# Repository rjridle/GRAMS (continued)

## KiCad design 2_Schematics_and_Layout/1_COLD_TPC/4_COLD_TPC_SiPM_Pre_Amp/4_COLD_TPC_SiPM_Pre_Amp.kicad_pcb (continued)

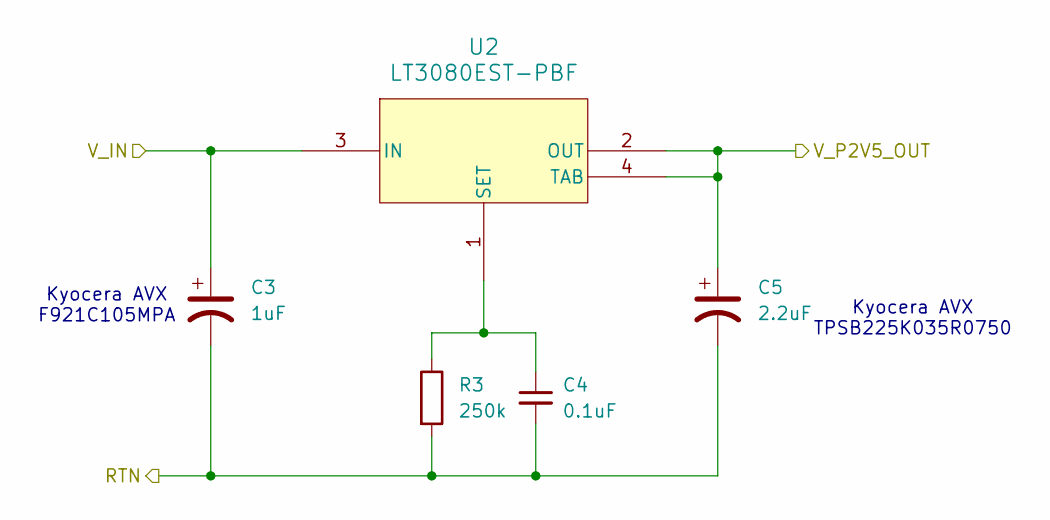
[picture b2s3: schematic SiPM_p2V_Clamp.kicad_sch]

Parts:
C3: 1uF; CP_EIA-2012-12_Kemet-R; Man. Part Num F921C105MPA
C4: 0.1uF; C_0603_1608Metric; Man. Part Num CC0603KRX7R7BB104
C5: 2.2uF; CP_EIA-3216-18_Kemet-A; Man. Part Num TAJA225K035RNJ
R3: 250k; R_0603_1608Metric; Man. Part Num P0603H2503BNT
U2: LT3080EST-PBF; SOT-3_ST_LIT; Man. Part Num LT3080EST#PBF

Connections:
/SiPM/SiPM_LV_Supply/SiPM_LV_5V/V_P5V_OUT: C3.2, C4.2, C5.2, R3.2; also elsewhere on the board
/SiPM/SiPM_LV_Supply/SiPM_LV_P3V3/V_P3V3_OUT: C3.1, U2.3 (IN); also elsewhere on the board
/SiPM/V_SiPM_LV_P2V5: C5.1, U2.2 (OUT), U2.4 (TAB); also elsewhere on the board
unnamed: C4.1, R3.1, U2.1 (SET)

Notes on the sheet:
Kyocera AVX F921C105MPA
Kyocera AVX TPSB225K035R0750

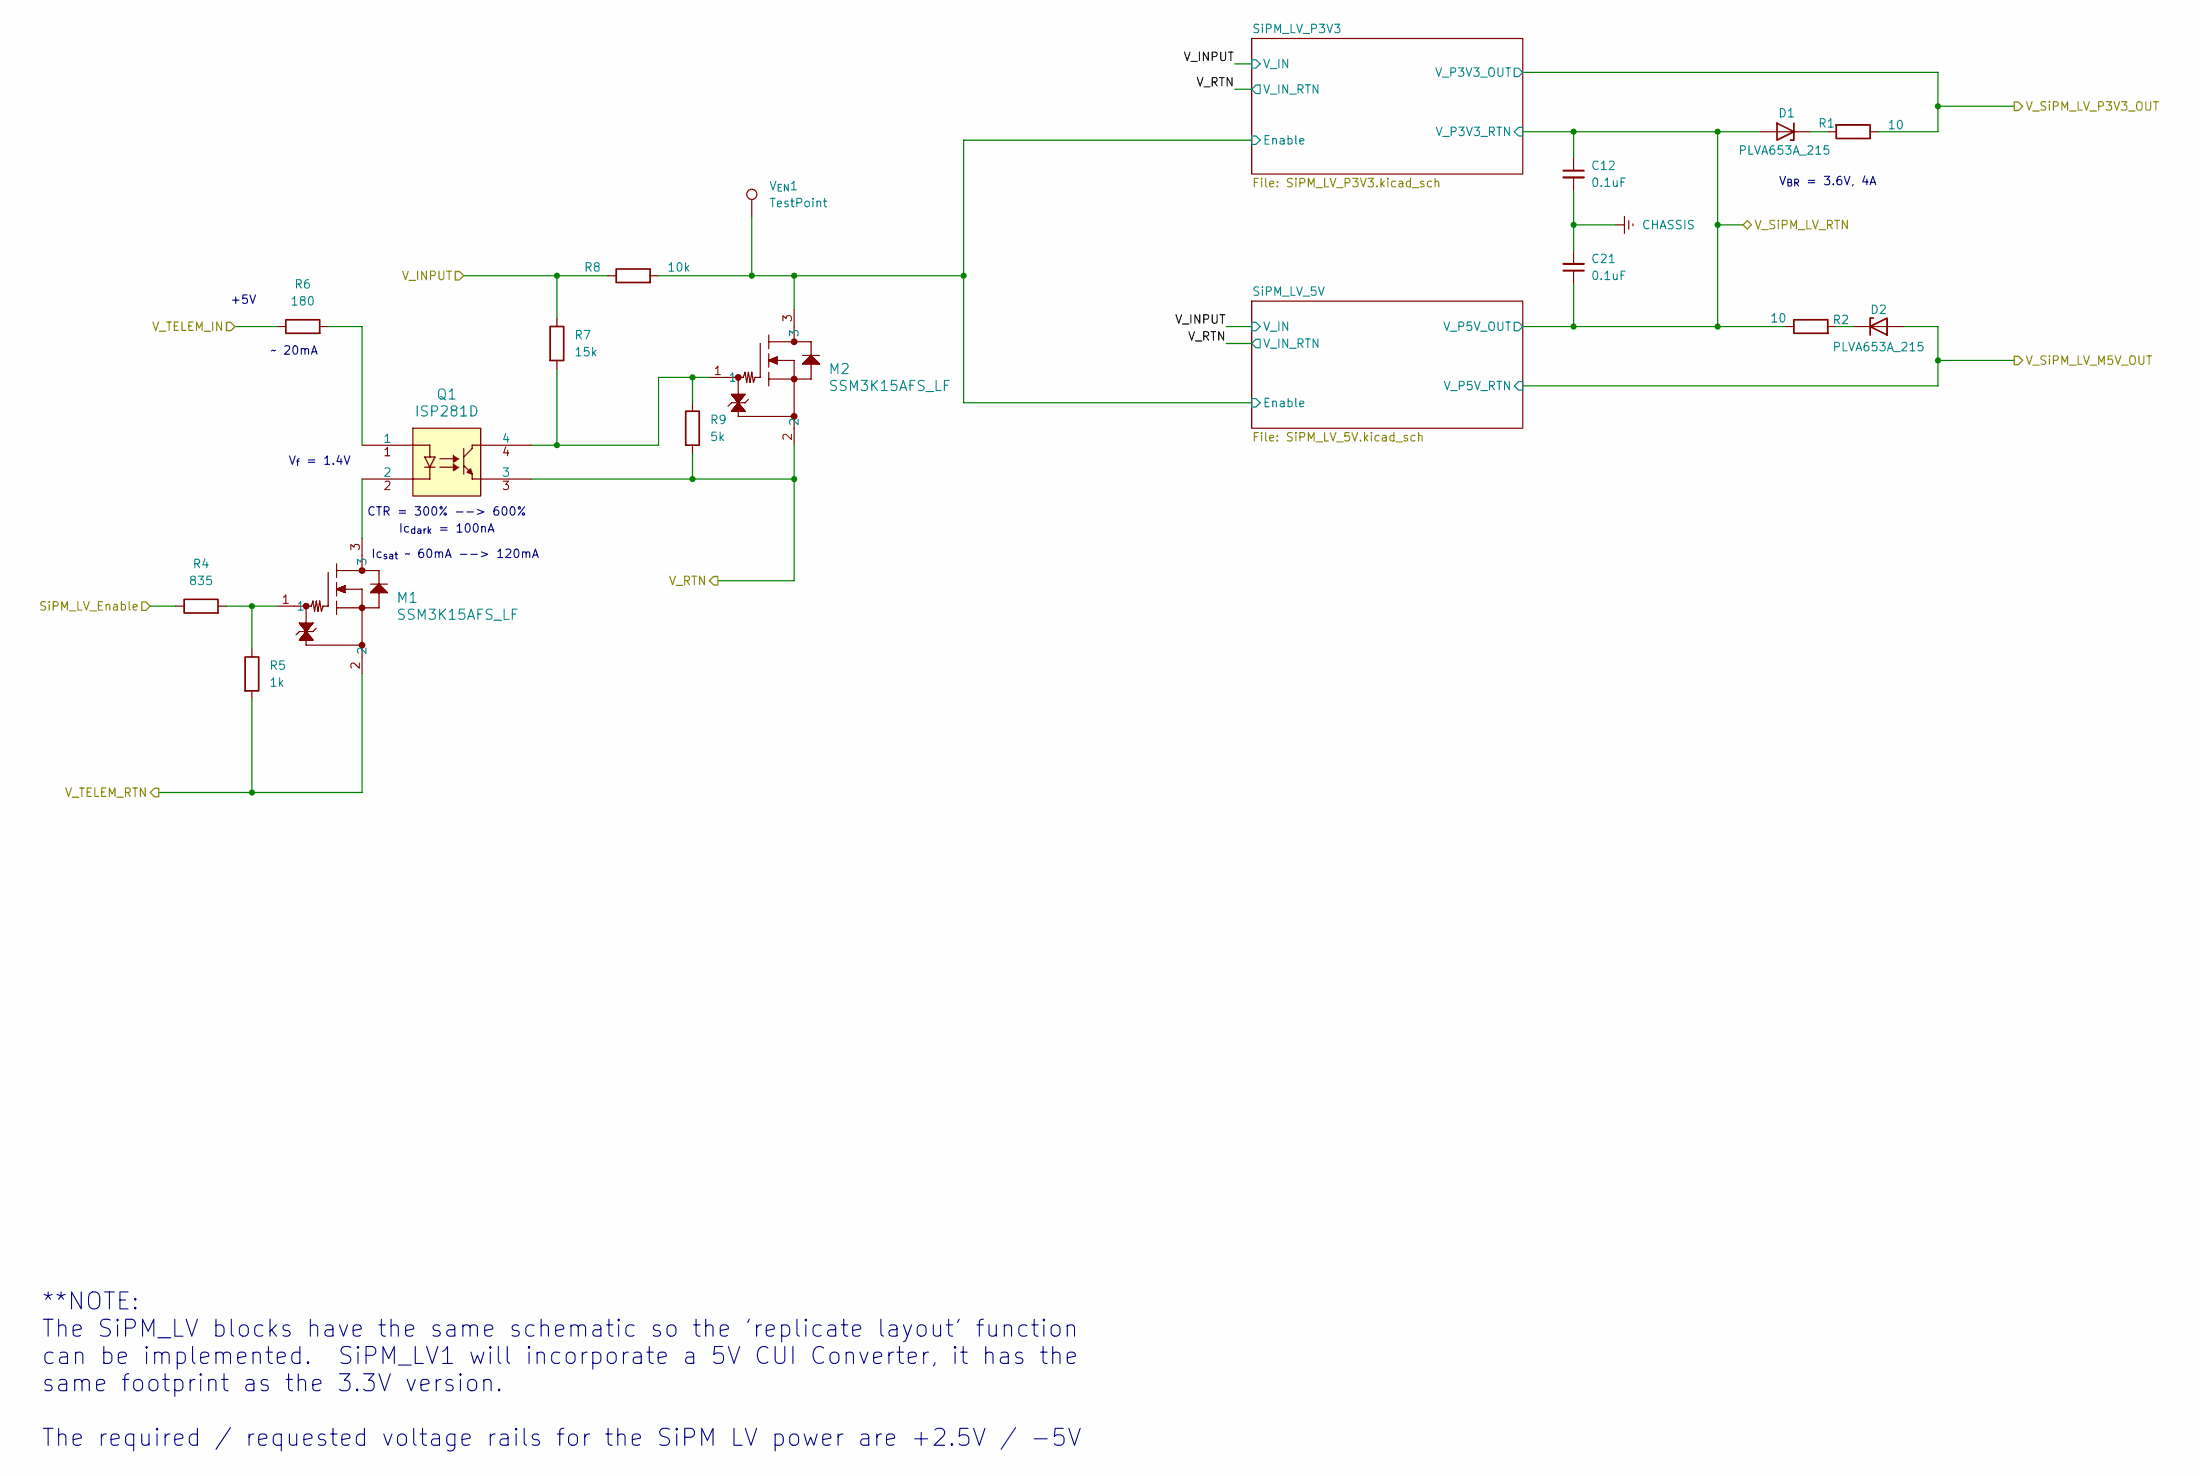
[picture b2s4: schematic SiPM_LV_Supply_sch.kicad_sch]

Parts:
C12, C21: 0.1uF; C_0603_1608Metric; Man. Part Num CC0603KRX7R7BB104
D1, D2: PLVA653A_215; SOT95P230X110-3N; Man. Part Num PLVA653A,215
M1, M2: SSM3K15AFS_LF; SSM_TOS; Man. Part Num SSM3K15AFS,LF
Q1: ISP281D; ISP281D_ISO; Man. Part Num ISP281D
R1, R2: 10; R_0603_1608Metric; Man. Part Num RMCF0603FT10R0
R4: 835; R_0603_1608Metric; Man. Part Num RN73H1JTTD8350A05
R5: 1k; R_0603_1608Metric; Man. Part Num RT0603BRD071KL
R6: 180; R_0603_1608Metric; Part Type SMD
R7: 15k; R_0603_1608Metric; Part Type SMD
R8: 10k; R_0603_1608Metric; Part Type SMD
R9: 5k; R_0603_1608Metric; Part Type SMD
V_{EN}1: TestPoint; TestPoint_Keystone_5005-5009_Compact; Man. Part Num 5008

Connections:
/P_SEC_TELEM_PWR: R6.1; also elsewhere on the board
/SEC_PWR_IN: R7.1, R8.1; also elsewhere on the board
/SEC_PWR_RTN: M2.2, Q1.3, R9.2; also elsewhere on the board
/SEC_PWR_TELEM_RTN: M1.2, R5.2; also elsewhere on the board
/SiPM/SiPM_LV_Supply/SiPM_LV_5V/Enable: M2.3, R8.2, V_{EN}1.1; also elsewhere on the board
/SiPM/SiPM_LV_Supply/SiPM_LV_5V/V_P5V_OUT: C12.1, C21.1, D1.1 (A), R2.1; also elsewhere on the board
/SiPM/SiPM_LV_Supply/SiPM_LV_Enable: R4.1; also elsewhere on the board
/SiPM/SiPM_LV_Supply/SiPM_LV_P3V3/V_P3V3_OUT: R1.1; also elsewhere on the board
/SiPM/V_SiPM_LV_M5V: D2.1 (A); also elsewhere on the board
CHASSIS: C12.2, C21.2; also elsewhere on the board
unnamed: D1.3 (K), R1.2
unnamed: D2.3 (K), R2.2
unnamed: M1.1, R4.2, R5.1
unnamed: M1.3, Q1.2
unnamed: M2.1, Q1.4, R7.2, R9.1
unnamed: Q1.1, R6.2

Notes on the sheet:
Ic_{dark} = 100nA
CTR = 300% --> 600%
~ 20mA
**NOTE: The SiPM_LV blocks have the same schematic so the 'replicate layout' function can be implemented. SiPM_LV1 will incorporate a 5V CUI Converter, it has the same footprint as the 3.3V version. The required / requested voltage rails for the SiPM LV power are +2.5V / -5V
V_{f} = 1.4V
Ic_{sat} ~ 60mA --> 120mA
+5V
V_{BR} = 3.6V, 4A

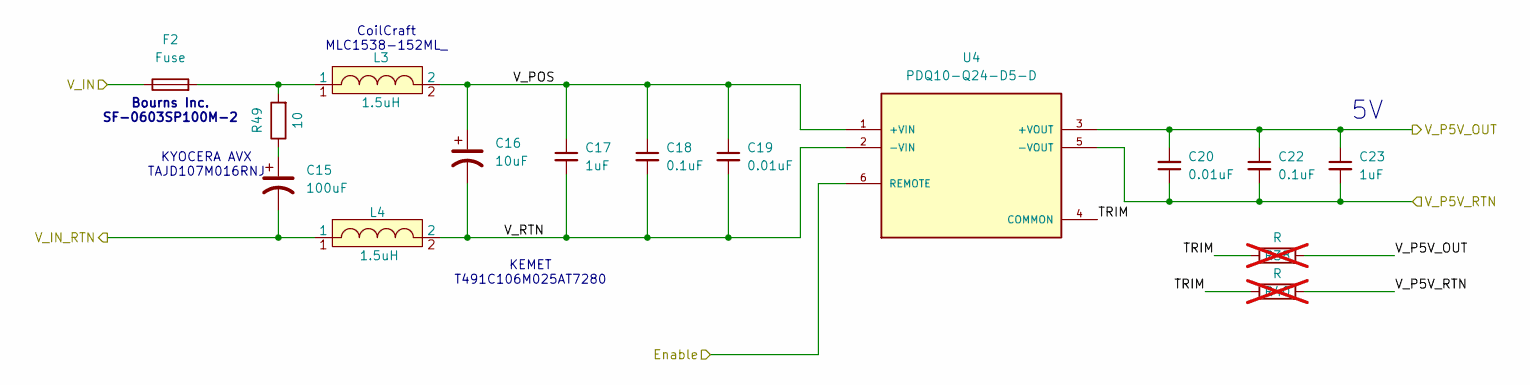
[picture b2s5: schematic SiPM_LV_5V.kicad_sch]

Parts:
C15: 100uF; CP_EIA-7343-20_Kemet-V; Man. Part Num TAJD107K016RNJ
C16: 10uF; CP_EIA-3216-12_Kemet-S; Man. Part Num T491A106M016AT
C17, C23: 1uF; C_0603_1608Metric; Man. Part Num CL10B105KO8NNNC
C18, C22: 0.1uF; C_0603_1608Metric; Man. Part Num CC0603KRX7R7BB104
C19, C20: 0.01uF; C_0603_1608Metric; Man. Part Num C0603C103K5RACTU
F2: Fuse; R_0603_1608Metric; Man. Part Num SF-0603SP100M-2
L3, L4: 1.5uH; MLC7542-311MEC; Man. Part Num MLC7540-142ME
R38, R40: R; R_0805_2012Metric; Part Type SMD; not fitted
R49: 10; R_0603_1608Metric; Man. Part Num RMCF0603FT10R0
U4: PDQ10-Q24-D5-D; CONV_PDQ10-Q24-D5-D; PARTREV 1.0

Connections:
/SEC_PWR_IN: F2.1; also elsewhere on the board
/SEC_PWR_RTN: C15.2, L4.1; also elsewhere on the board
/SiPM/SiPM_LV_Supply/SiPM_LV_5V/Enable: U4.6 (REMOTE); also elsewhere on the board
/SiPM/SiPM_LV_Supply/SiPM_LV_5V/TRIM: R38.1, R40.1, U4.4 (COMMON)
/SiPM/SiPM_LV_Supply/SiPM_LV_5V/V_P5V_OUT: C20.2, C22.1, C23.1, R38.2, U4.3 (+VOUT); also elsewhere on the board
/SiPM/SiPM_LV_Supply/SiPM_LV_5V/V_POS: C16.1, C17.1, C18.1, C19.1, L3.2, U4.1 (+VIN)
/SiPM/SiPM_LV_Supply/SiPM_LV_5V/V_RTN: C16.2, C17.2, C18.2, C19.2, L4.2, U4.2 (-VIN)
/SiPM/V_SiPM_LV_M5V: C20.1, C22.2, C23.2, R40.2, U4.5 (-VOUT); also elsewhere on the board
unnamed: C15.1, R49.1
unnamed: F2.2, L3.1, R49.2

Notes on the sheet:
CoilCraft MLC1538-152ML_
KEMET T491C106M025AT7280
Bourns Inc. SF-0603SP100M-2
KYOCERA AVX TAJD107M016RNJ

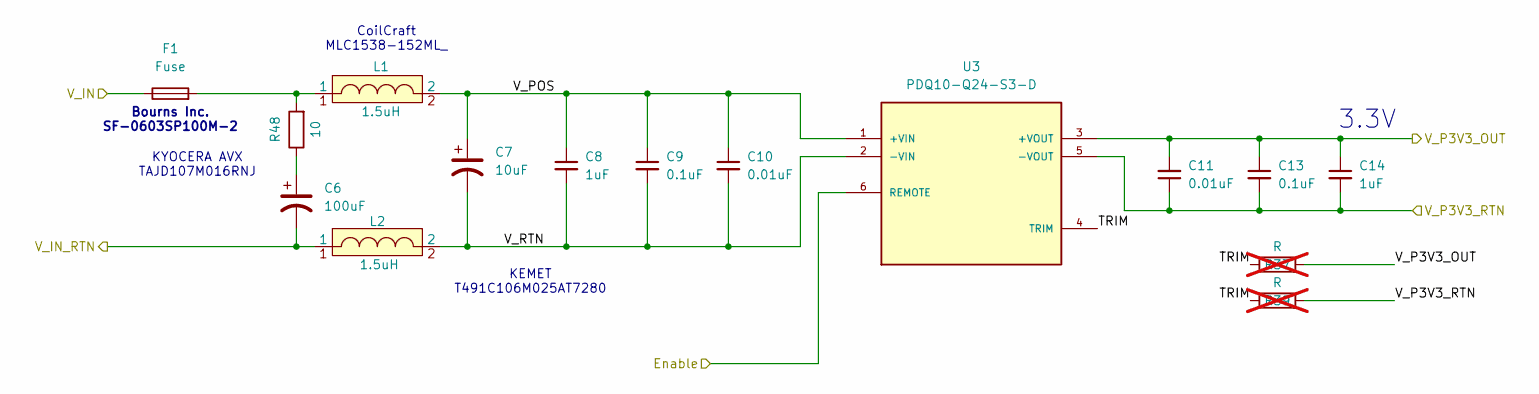
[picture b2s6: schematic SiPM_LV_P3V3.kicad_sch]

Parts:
C6: 100uF; CP_EIA-7343-20_Kemet-V; Man. Part Num TAJD107K016RNJ
C7: 10uF; CP_EIA-3216-12_Kemet-S; Man. Part Num T491A106M016AT
C8, C14: 1uF; C_0603_1608Metric; Man. Part Num CL10B105KO8NNNC
C9, C13: 0.1uF; C_0603_1608Metric; Man. Part Num CC0603KRX7R7BB104
C10, C11: 0.01uF; C_0603_1608Metric; Man. Part Num C0603C103K5RACTU
F1: Fuse; R_0603_1608Metric; Man. Part Num SF-0603SP100M-2
L1, L2: 1.5uH; MLC7542-311MEC; Man. Part Num MLC7540-142ME
R37, R39: R; R_0805_2012Metric; Part Type SMD; not fitted
R48: 10; R_0603_1608Metric; Man. Part Num RMCF0603FT10R0
U3: PDQ10-Q24-S3-D; CONV_PDQ10-Q24-S3-D; PARTREV 1.0

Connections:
/SEC_PWR_IN: F1.1; also elsewhere on the board
/SEC_PWR_RTN: C6.2, L2.1; also elsewhere on the board
/SiPM/SiPM_LV_Supply/SiPM_LV_5V/Enable: U3.6 (REMOTE); also elsewhere on the board
/SiPM/SiPM_LV_Supply/SiPM_LV_5V/V_P5V_OUT: C11.1, C13.2, C14.2, R39.2, U3.5 (-VOUT); also elsewhere on the board
/SiPM/SiPM_LV_Supply/SiPM_LV_P3V3/TRIM: R37.1, R39.1, U3.4 (TRIM)
/SiPM/SiPM_LV_Supply/SiPM_LV_P3V3/V_P3V3_OUT: C11.2, C13.1, C14.1, R37.2, U3.3 (+VOUT); also elsewhere on the board
/SiPM/SiPM_LV_Supply/SiPM_LV_P3V3/V_POS: C7.1, C8.1, C9.1, C10.1, L1.2, U3.1 (+VIN)
/SiPM/SiPM_LV_Supply/SiPM_LV_P3V3/V_RTN: C7.2, C8.2, C9.2, C10.2, L2.2, U3.2 (-VIN)
unnamed: C6.1, R48.1
unnamed: F1.2, L1.1, R48.2

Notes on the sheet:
Bourns Inc. SF-0603SP100M-2
KYOCERA AVX TAJD107M016RNJ
KEMET T491C106M025AT7280
CoilCraft MLC1538-152ML_
3.3V

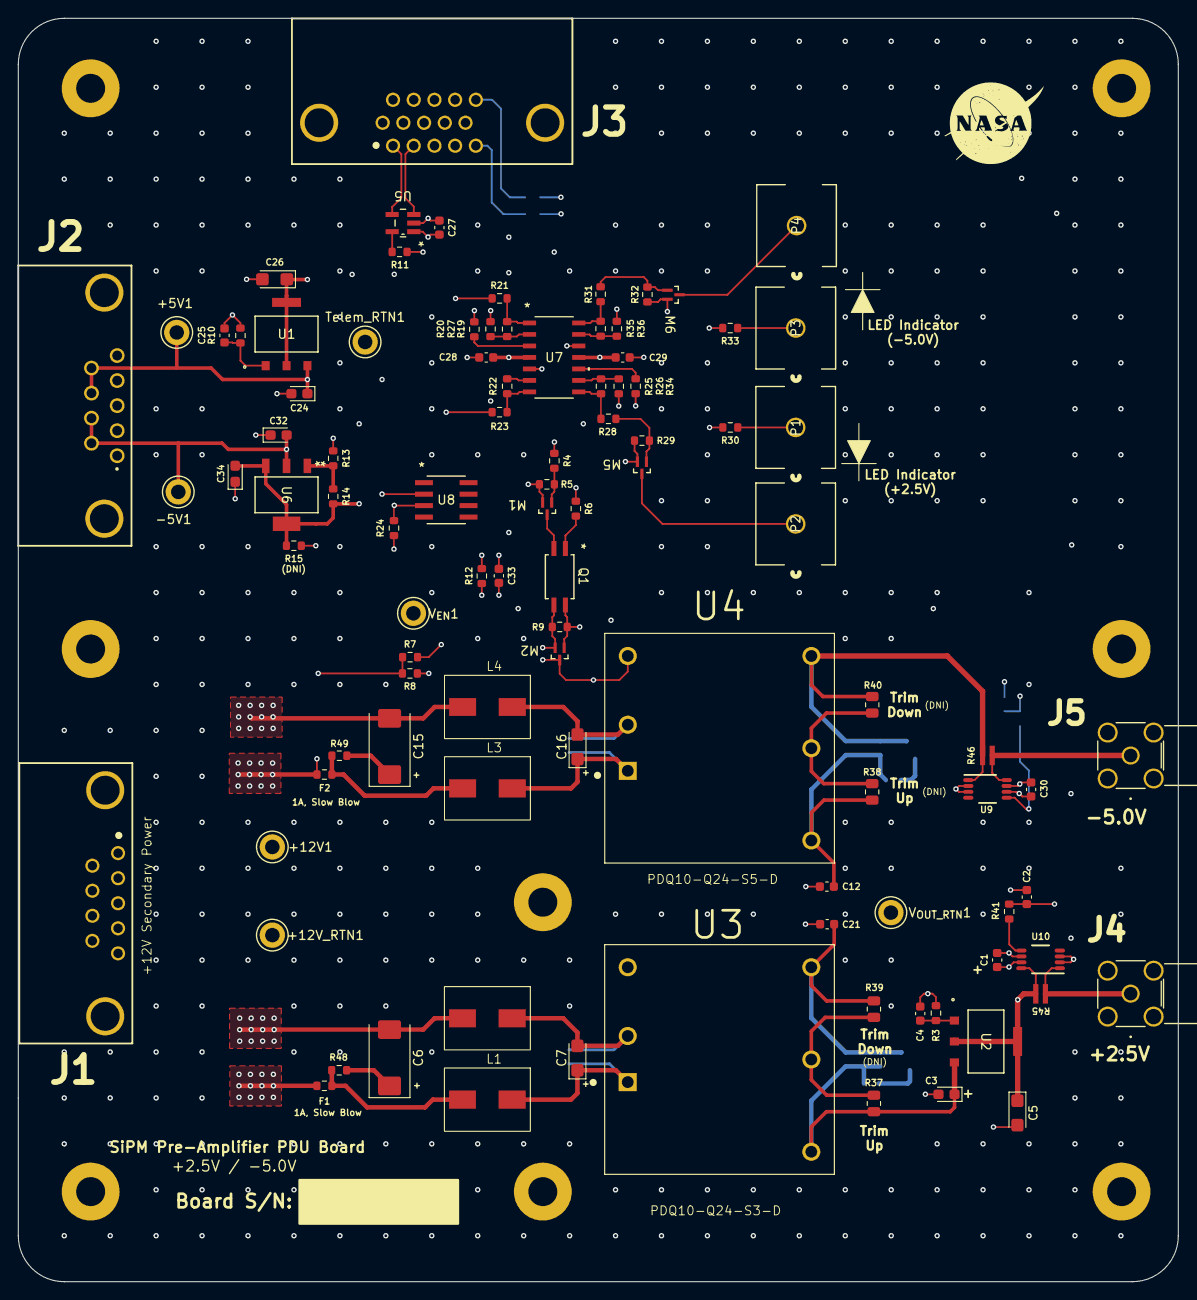
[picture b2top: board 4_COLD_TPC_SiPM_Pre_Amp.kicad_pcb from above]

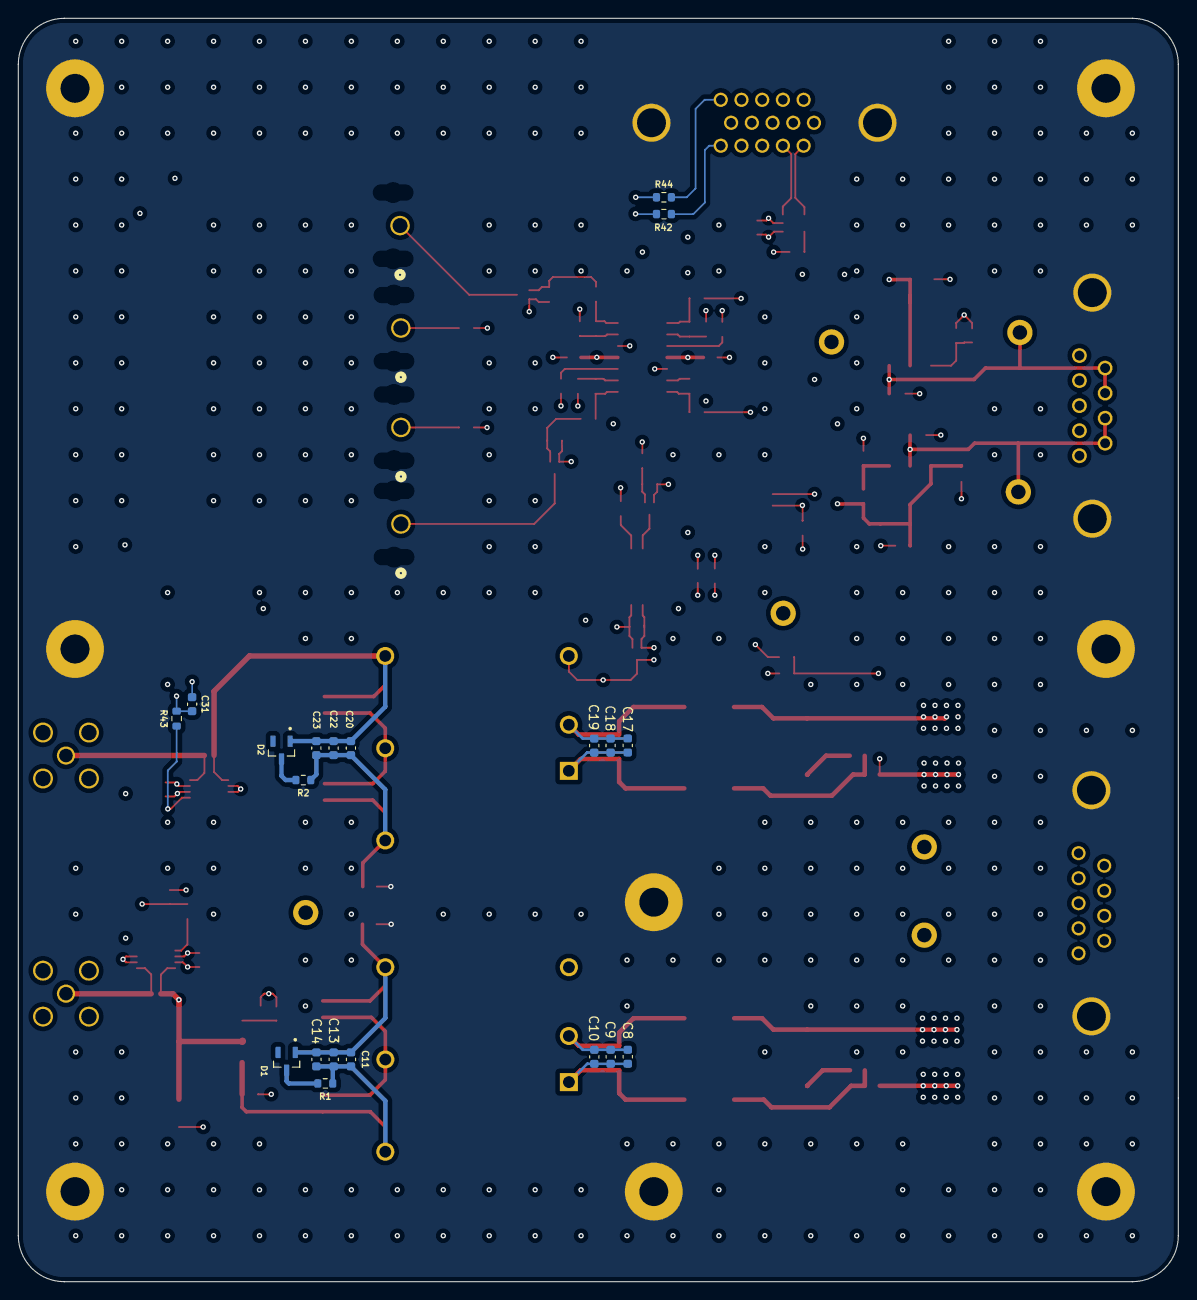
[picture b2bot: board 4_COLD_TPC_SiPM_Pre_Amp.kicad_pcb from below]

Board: 10 copper layers, 128.3 x 139.7 mm, 126 parts (20 on the bottom side), 63 nets.

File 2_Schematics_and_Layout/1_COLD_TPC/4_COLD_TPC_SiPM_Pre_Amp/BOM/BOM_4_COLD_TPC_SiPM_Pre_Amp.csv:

"Reference","Value","Footprint","Qty","DNP","Manufacturer","Man. Part Num","Distributor","Dist. Part Num"
"+5V1,+12V1","TestPoint","TestPoint:TestPoint_Keystone_5005-5009_Compact","2","","Keystone Electronics","5005","Digi-Key","36-5005-ND"
"+12V_RTN1,Telem_RTN1,V_{OUT_RTN}1","TestPoint","TestPoint:TestPoint_Keystone_5005-5009_Compact","3","","Keystone Electronics,Wurth Electronics","5006","Digi-Key","36-5006-ND"
"-5V1","TestPoint","TestPoint:TestPoint_Keystone_5005-5009_Compact","1","","Keystone Electronics","5009","Digi-Key","36-5009-ND"
"C1,C4,C9,C12,C13,C18,C21,C22,C25,C27,C28,C29,C30,C33","0.1uF","Capacitor_SMD:C_0603_1608Metric","14","","YAGEO","CC0603KRX7R7BB104","Digi-Key","311-1088-1-ND"
"C2,C8,C14,C17,C23,C31","1uF","Capacitor_SMD:C_0603_1608Metric","6","","Samsung Electro-Mechanics","CL10B105KO8NNNC","Digi-Key","1276-1019-1-ND"
"C3,C24,C32,C34","1uF","Capacitor_Tantalum_SMD:CP_EIA-2012-12_Kemet-R","4","","KYOCERA AVX","F921C105MPA","Digi-Key","478-8126-1-ND"
"C5,C26","2.2uF","Capacitor_Tantalum_SMD:CP_EIA-3216-10_Kemet-I,Capacitor_Tantalum_SMD:CP_EIA-3216-18_Kemet-A","2","","KYOCERA AVX","TAJA225K035RNJ","Digi-Key","478-3073-1-ND"
"C6,C15","100uF","Capacitor_Tantalum_SMD:CP_EIA-7343-20_Kemet-V","2","","KYOCERA AVX","TAJD107K016RNJ","Digi-Key","478-1723-1-ND"
"C7,C16","10uF","Capacitor_Tantalum_SMD:CP_EIA-3216-12_Kemet-S","2","","KYOCERA AVX","T491A106M016AT","Digi-Key","399-3687-1-ND"
"C10,C11,C19,C20","0.01uF","Capacitor_SMD:C_0603_1608Metric","4","","KEMET","C0603C103K5RACTU","Digi-Key","399-C0603C103K5RACTUCT-ND"
"D1,D2","PLVA653A_215","Nexperia:SOT95P230X110-3N","2","","Nexperia USA Inc.","PLVA653A,215","Digi-Key","1727-5168-1-ND"
"F1,F2","Fuse","Resistor_SMD:R_0603_1608Metric","2","","Bourns Inc.","SF-0603SP100M-2","Digi-Key","SF-0603SP100M-2CT-ND"
"J1","618009231221","Wurth_Elektronik:618009231221","1","","Wurth Electronics","618009231221","Digi-Key","732-618009231221-ND"
"J2","618009231121","Wurth_Elektronik:618009231121","1","","Wurth Electronics","618009231121","Digi-Key","732-618009231121-ND"
"J3","618015330923","Wurth_Elektronik:618015330923","1","","Wurth Electronics","618015330923","Digi-Key","732-618015330923-ND"
"J4,J5","RF2-49B-T-00-50-G-HDW","Adam_Tech:CONN_RF2-49B-T-00-50-G-HDW_ADM","2","","Adam Tech","RF2-49B-T-00-50-G-HDW","Digi-Key","2057-RF2-49B-T-00-50-G-HDW-ND"
"L1,L2,L3,L4","1.5uH","CoilCraft:MLC7542-311MEC","4","","Coil Craft","MLC7540-142ME","Digi-Key","MLC7540-142ME"
"M1,M2,M5,M6","SSM3K15AFS_LF","Toshiba_Semi:SSM_TOS","4","","Toshiba Semiconductor and Storage","SSM3K15AFS,LF","Digi-Key","SSM3K15AFSLFCT-ND"
"P1,P2,P3,P4","1-1123824-1","TE_Connectivity:conn1_1-1123824-1_TEC","4","","TE Connectivity AMP Connectors","1-1123824-1","Digi-Key","A30708-ND"
"Q1","ISP281D","ISOCOM:ISP281D_ISO","1","","Isocom Components 2004 LTD","ISP281D","Digi-Key","58-ISP281DCT-ND"
"R1,R2,R48,R49","10","Resistor_SMD:R_0603_1608Metric","4","","Stackpole Electronics Inc","RMCF0603FT10R0","Digi-Key","RMCF0603FT10R0CT-ND"
"R3","250k","Resistor_SMD:R_0603_1608Metric","1","","Vishay Sfernice","P0603H2503BNT","Digi-Key","716-P0603H2503BNTCT-ND"
"R4","835","Resistor_SMD:R_0603_1608Metric","1","","KOA Speer Electronics, Inc.","RN73H1JTTD8350A05","Digi-Key","2019-RN73H1JTTD8350A05CT-ND"
"R5,R12","1k","Resistor_SMD:R_0603_1608Metric","2","","YAGEO","RT0603BRD071KL","Digi-Key","YAG1237CT-ND"
"R6","180","Resistor_SMD:R_0603_1608Metric","1","","Vishay Beyschlag/Draloric/BC Components","MCT06030C1800FP500","Digi-Key","749-1612-1-ND"
"R7","15k","Resistor_SMD:R_0603_1608Metric","1","","Panasonic Electronic Components","ERA-3AEB153V","Digi-Key","P15KDBCT-ND"
"R8,R19,R22,R26,R35","10k","Resistor_SMD:R_0603_1608Metric","5","","Stackpole Electronics Inc","RNCP0603FTD10K0","Digi-Key","RNCP0603FTD10K0CT-ND"
"R9,R25","5k","Resistor_SMD:R_0603_1608Metric","2","","YAGEO","RT0603BRE075KL","Digi-Key","13-RT0603BRE075KLCT-ND"
"R10","330k","Resistor_SMD:R_0603_1608Metric","1","","Susumu","RG1608P-334-B-T5","Digi-Key","RG16P330KBCT-ND"
"R11,R21,R23,R28,R31,R34","49.9","Resistor_SMD:R_0603_1608Metric","6","","Stackpole Electronics Inc","RNCP0603FTD49R9","Digi-Key","RNCP0603FTD49R9CT-ND"
"R13","196","Resistor_SMD:R_0603_1608Metric","1","","Panasonic Electronic Components","ERA-3AEB1960V","Digi-Key","P196DBCT-ND"
"R14,R15","120","Resistor_SMD:R_0603_1608Metric","2","","YAGEO","RT0603DRE07120RL","Digi-Key","311-2409-1-ND"
"R20,R41,R42,R43,R44","24.9","Resistor_SMD:R_0603_1608Metric","5","","Stackpole Electronics Inc","RNCF0603TKY24R9","Digi-Key","RNCF0603TKY24R9CT-ND"
"R24","8k","Resistor_SMD:R_0603_1608Metric","1","","YAGEO","RT0603BRE078KL","Digi-Key","13-RT0603BRE078KLCT-ND"
"R27","20k","Resistor_SMD:R_0603_1608Metric","1","","Vishay Dale","TNPW060320K0BEEA","Digi-Key","TNP20.0KAACT-ND"
"R29,R32","100k","Resistor_SMD:R_0603_1608Metric","2","","Vishay Dale","TNPW0603100KBEEA","Digi-Key","TNP100KAACT-ND"
"R30,R33","150","Resistor_SMD:R_0603_1608Metric","2","","Panasonic Electronic Components","ERA-3AEB151V","Digi-Key","P150DBCT-ND"
"R36","40k","Resistor_SMD:R_0603_1608Metric","1","","Vishay Dale Thin Film","PAT0603E4002BST1","Digi-Key","PAT40KACT-ND"
"R37,R38,R39,R40","R","Resistor_SMD:R_0805_2012Metric","4","","DO NOT POPULATE","DO NOT POPULATE","",""
"R45,R46","FCSL20R010FER","Foil_Resistors:RES_FCSL20_OHM-L","2","","Ohmite","FCSL20R010FER","Digi-Key","FCSL20R010FERCT-ND"
"U1,U2","LT3080EST-PBF","Analog_Devices:SOT-3_ST_LIT","2","","Analog Devices Inc.","LT3080EST#PBF","Digi-Key","505-LT3080EST#PBF-ND"
"U3,U4","PDQ10-Q24-S3-D","CUI:CONV_PDQ10-Q24-S3-D","2","","CUI Inc.","PDQ10-Q24-S3-D","Digi-Key","102-3868-ND"
"U5","SN65LVDS2DBVR","Texas_Instruments:DBV5","1","","Texas Instruments","SN65LVDS2DBVR","Digi-Key","296-6920-1-ND"
"U6","LM337IMPX/NOPB","Texas_Instruments:LM337IMPX","1","","Texas Instruments","LM337IMPX/NOPB","Mouser","926-LM337IMPX/NOPB"
"U7","LTC2052HVCS","Analog_Devices:SO-14_S_LIT","1","","Analog Devices Inc.","LTC2052HVCS#PBF","Digi-Key","LTC2052HVCS#PBF-ND"
"U8","AD590JRZ-RL","Analog_Devices:R_8_ADI","1","","Analog Devices Inc.","AD590JRZ","Digi-Key","AD590JRZ-ND"
"U9,U10","INA286","INA285AQDRQ1:SOIC127P599X175-8N","2","","Texas Instruments","INA286AIDR","Digi-Key","296-43593-1-ND"
"V_{EN}1","TestPoint","TestPoint:TestPoint_Keystone_5005-5009_Compact","1","","Wurth Electronics","5008","Digi-Key","36-5008-ND"

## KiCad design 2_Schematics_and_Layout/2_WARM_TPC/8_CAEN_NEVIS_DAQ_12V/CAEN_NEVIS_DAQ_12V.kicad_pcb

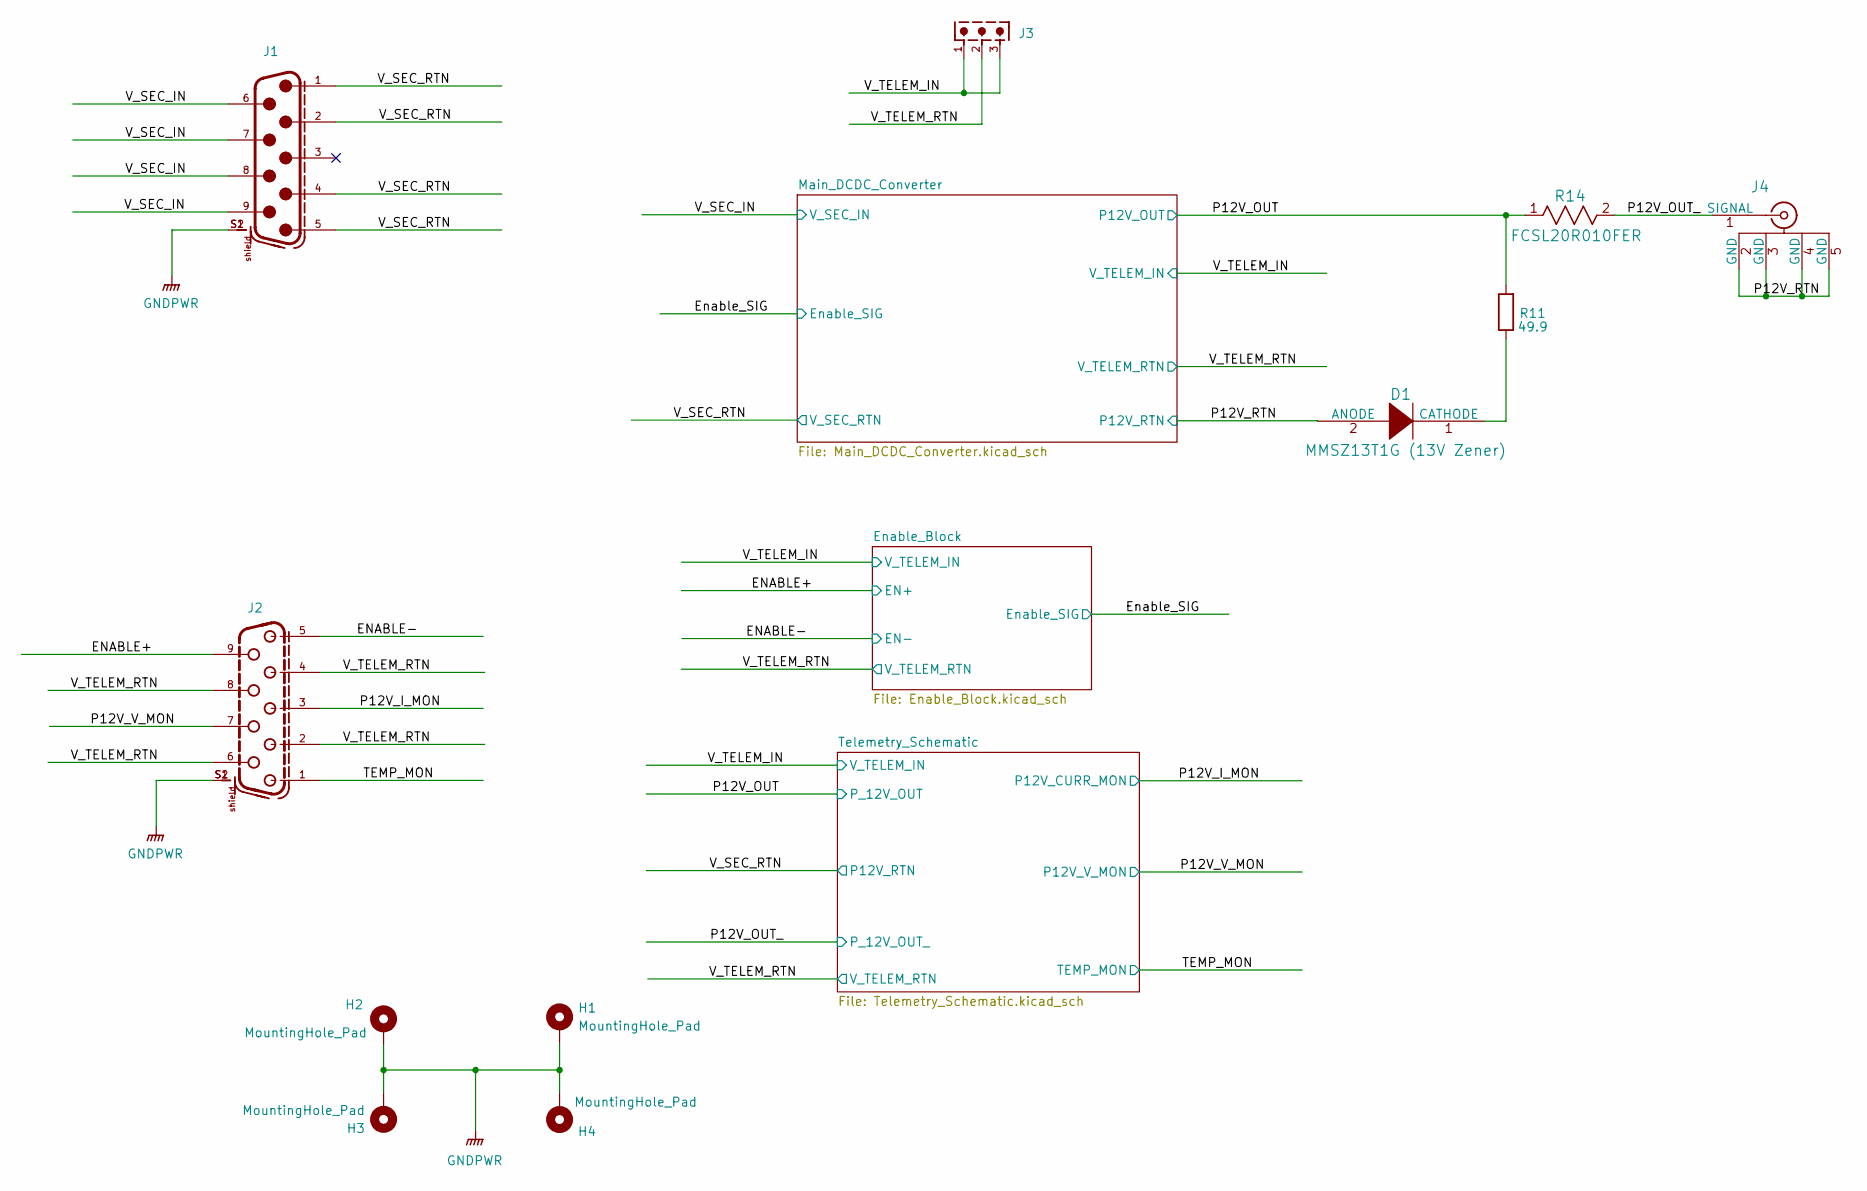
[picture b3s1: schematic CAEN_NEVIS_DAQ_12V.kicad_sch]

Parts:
D1: MMSZ13T1G (13V Zener); SOD-123_ONS-L; Man. Part Num MMSZ13T1G
H1, H2, H3, H4: MountingHole_Pad; MountingHole_3.2mm_M3_Pad
J1: 618009231221; PART-NUMBER 618009231221
J2: 618009231121; PART-NUMBER 618009231121
J3: 691322310003; Part Type Through Hole
J4: RF2-49B-T-00-50-G-HDW; CONN_RF2-49B-T-00-50-G-HDW_ADM; Man. Part Num RF2-49B-T-00-50-G-HDW
R11: 49.9; R_0603_1608Metric; Man. Part Num TNPW060349R9BEEA
R14: FCSL20R010FER; RES_FCSL20_OHM-L; Man. Part Num FCSL20R010FER

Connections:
/ENABLE+: J2.9; also elsewhere on the board
/ENABLE-: J2.5; also elsewhere on the board
/P12V_I_MON: J2.3; also elsewhere on the board
/P12V_OUT: R11.2, R14.1; also elsewhere on the board
/P12V_OUT_: J4.1 (SIGNAL), R14.2; also elsewhere on the board
/P12V_RTN: D1.2 (ANODE), J4.2 (GND), J4.3 (GND), J4.4 (GND), J4.5 (GND); also elsewhere on the board
/P12V_V_MON: J2.7; also elsewhere on the board
/TEMP_MON: J2.1; also elsewhere on the board
/V_SEC_IN: J1.6, J1.7, J1.8, J1.9; also elsewhere on the board
/V_SEC_RTN: J1.1, J1.2, J1.4, J1.5; also elsewhere on the board
/V_TELEM_IN: J3.1, J3.3; also elsewhere on the board
/V_TELEM_RTN: J2.2, J2.4, J2.6, J2.8, J3.2; also elsewhere on the board
GNDPWR: H1.1, H2.1, H3.1, H4.1, J1.S1, J1.S2, J2.S1, J2.S2; also elsewhere on the board
unnamed: D1.1 (CATHODE), R11.1

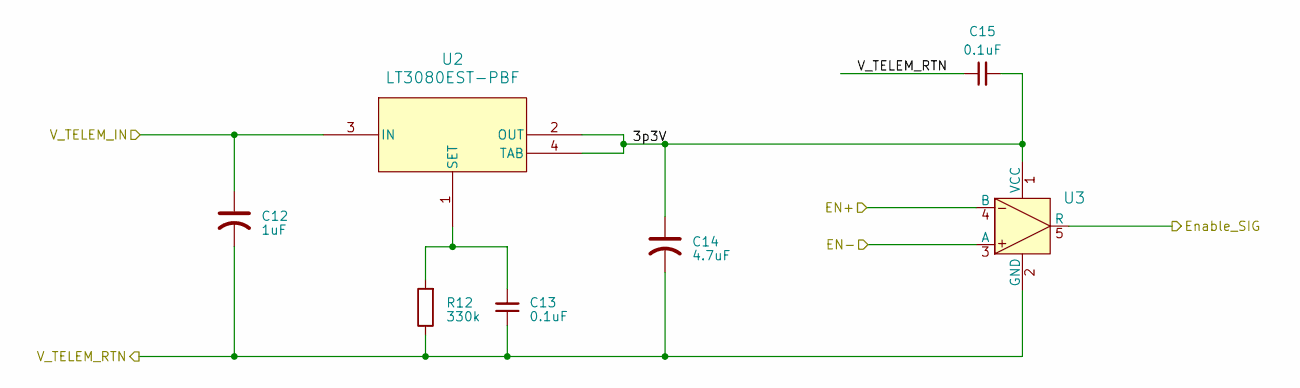
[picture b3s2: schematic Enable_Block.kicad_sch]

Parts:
C12: 1uF; CP_EIA-3216-10_Kemet-I; Man. Part Num TAJA105K016RNJ
C13: 0.1uF; C_0603_1608Metric; Man. Part Num CC0603KRX7R7BB104
C14: 4.7uF; CP_EIA-3216-10_Kemet-I; Man. Part Num TAJA475K016RNJ
C15: 0.1uF; C_0402_1005Metric; Man. Part Num CL05B104KP5NNNC
R12: 330k; R_0603_1608Metric; Man. Part Num ERA-3AEB334V
U2: LT3080EST-PBF; SOT-3_ST_LIT; Man. Part Num LT3080EST#PBF
U3: SN65LVDS2DBVR; DBV5; Man. Part Num SN65LVDS2DBVR

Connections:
/ENABLE+: U3.4 (B); also elsewhere on the board
/ENABLE-: U3.3 (A); also elsewhere on the board
/Enable_Block/3p3V: C14.1, C15.2, U2.2 (OUT), U2.4 (TAB), U3.1 (VCC)
/Enable_SIG: U3.5 (R); also elsewhere on the board
/V_TELEM_IN: C12.1, U2.3 (IN); also elsewhere on the board
/V_TELEM_RTN: C12.2, C13.1, C14.2, C15.1, R12.1, U3.2 (GND); also elsewhere on the board
unnamed: C13.2, R12.2, U2.1 (SET)

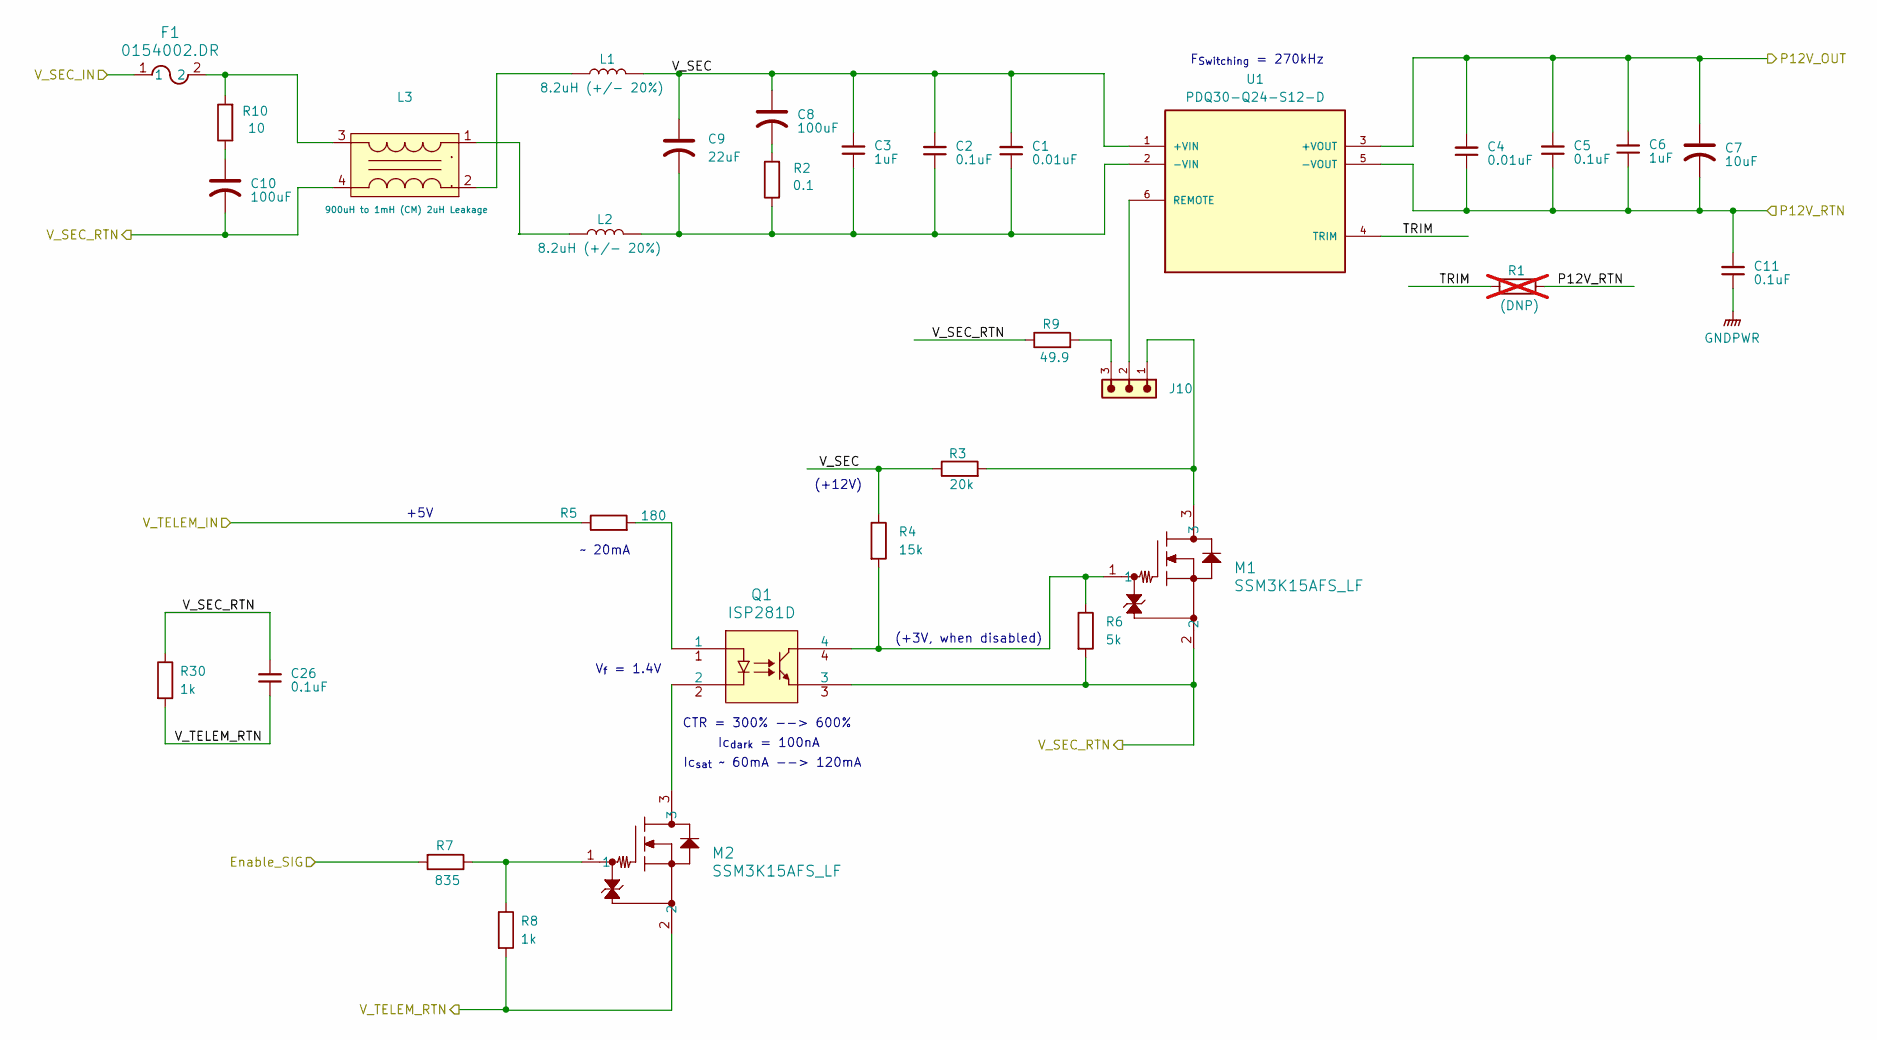
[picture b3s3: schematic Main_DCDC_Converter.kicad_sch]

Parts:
C1, C4: 0.01uF; C_0603_1608Metric; Man. Part Num C0603C103K5RACTU
C2, C5, C11, C26: 0.1uF; C_0603_1608Metric; Man. Part Num CC0603KRX7R8BB104
C3, C6: 1uF; C_0603_1608Metric; Man. Part Num CL10B105KO8NNNC
C7: 10uF; CP_EIA-6032-20_AVX-F; Man. Part Num TAJC106K025RNJ
C8, C10: 100uF; CP_EIA-6032-20_AVX-F; Man. Part Num TAJC107K016RNJ
C9: 22uF; CP_EIA-3528-12_Kemet-T; Man. Part Num T491B226K020AT
F1: 0154002.DR; 0154Series_LTF; Man. Part Num 0154002.DR
J10: 61300311121; PART-NUMBER 61300311121
L1, L2: 8.2uH (+/- 20%); LPS6235-822MR; Man. Part Num LPS6235-822MR
L3: 900uH to 1mH (CM) 2uH Leakage; MSD1583-105; Man. Part Num MSD1583-105KE_
M1, M2: SSM3K15AFS_LF; SSM_TOS; Man. Part Num SSM3K15AFS,LF
Q1: ISP281D; ISP281D_ISO; Man. Part Num ISP281D
R1: (DNP); R_0603_1608Metric; Part Type SMD; not fitted
R2: 0.1; R_0603_1608Metric; Man. Part Num RL0805FR-070R1L
R3: 20k; R_0603_1608Metric; Man. Part Num ERA-3AEB203V
R4: 15k; R_0603_1608Metric; Man. Part Num ERA-3AEB153V
R5: 180; R_0603_1608Metric; Man. Part Num TNPW0603180RBEEA
R6: 5k; R_0603_1608Metric; Man. Part Num RT0603BRE075KL
R7: 835; R_0603_1608Metric; Man. Part Num RN73H1JTTD8350A05
R8, R30: 1k; R_0603_1608Metric; Man. Part Num RMCF0603FT1K00
R9: 49.9; R_0603_1608Metric; Man. Part Num TNPW060349R9BEEA
R10: 10; R_0805_2012Metric; Man. Part Num CRGH0805F10R
U1: PDQ30-Q24-S12-D; Man. Part Num PDQ30-Q24-S12-D

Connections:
/Enable_SIG: R7.2; also elsewhere on the board
/Main_DCDC_Converter/TRIM: R1.1, U1.4 (TRIM)
/Main_DCDC_Converter/V_SEC: C1.2, C2.2, C3.2, C8.1, C9.1, L1.2, R3.1, R4.1, U1.1 (+VIN)
/P12V_OUT: C4.2, C5.2, C6.2, C7.1, U1.3 (+VOUT); also elsewhere on the board
/P12V_RTN: C4.1, C5.1, C6.1, C7.2, C11.2, R1.2, U1.5 (-VOUT); also elsewhere on the board
/V_SEC_IN: F1.1; also elsewhere on the board
/V_SEC_RTN: C10.2, C26.2, L3.4, M1.2, Q1.3, R6.2, R9.1, R30.1; also elsewhere on the board
/V_TELEM_IN: R5.1; also elsewhere on the board
/V_TELEM_RTN: C26.1, M2.2, R8.2, R30.2; also elsewhere on the board
GNDPWR: C11.1; also elsewhere on the board
unnamed: C8.2, R2.2
unnamed: C10.1, R10.1
unnamed: F1.2, L3.3, R10.2
unnamed: J10.1, M1.3, R3.2
unnamed: J10.3, R9.2
unnamed: L1.1, L3.2
unnamed: L2.1, L3.1
unnamed: M1.1, Q1.4, R4.2, R6.1
unnamed: M2.1, R7.1, R8.1
unnamed: M2.3, Q1.2
unnamed: Q1.1, R5.2
unnamed: C1.1, C2.1, C3.1, C9.2, L2.2, R2.1, U1.2 (-VIN)
unnamed: J10.2, U1.6 (REMOTE)

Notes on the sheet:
(+12V)
V_{f} = 1.4V
Ic_{dark} = 100nA
(+3V, when disabled)
~ 20mA
+5V
F_{Switching} = 270kHz
Ic_{sat} ~ 60mA --> 120mA
CTR = 300% --> 600%
